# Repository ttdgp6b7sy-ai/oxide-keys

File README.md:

# Oxide Keys

A mini game console with 8 keys and a display, which has the ability to play very simple games to kill time and also a fun way to integrate Rust (the language I am learning).

The hardware is mainly composed of an 8-key mini game player with rotary encoder, LCD display that folds on a hinge, and RGB underglow on the Raspberry Pi Pico W, where I aim to include as much Rust as I can in this project.

## CAD views

[Assembly STEP](cad/OxideKeys-review-assembly-detailed.step) · [Enclosure SVG](cad/Oxidekeysenclosure.svg)

## Demo
No physical build yet but the image above shows the PCB board to be made.

## Location of stuff
- `firmware/` Rust code for the Pico W
- `pcb/` KiCad project and gerbers
- `cad/` 3D model and layout for enclosure
- `BOM.csv` parts list

## Quickstart

**Get the files**
Clone the repo or download extract zip from github repo.
`git clone https://github.com/ttdgp6b7sy-ai/oxide-keys.git`
`cd oxide-keys`

**Flash the firmware**
1. Hold the bootsel button on the pico W while plugging it into USB, it will appear as a drive.
2. Drag `firmware/oxide-keys.uf2` onto that drive and then it reboots on its own.

**Build the firmware yourself**
1. install rust from https://rustup.rs if you haven't already
2. `rustup target add thumbv6m-none-eabi`
3. `cargo install flip-link elf2uf2-rs --locked`
4. `cd firmware`, then `cargo build --release`
5.  convert to UF2: `elf2uf2-rs target/thumbv6m-none-eabi/release/oxide-keys oxide-keys.uf2`, then drag it onto the pico as above

**3d model**
The full assembly is `cad/OxideKeys-review-assembly-detailed.step`

## Features that I will implement
- The switches are designed so that each key is important in navigating the screen where I want to create a launcher which you can scroll through a section of simple games similar to pong and space invader that I create. These keys will be assigned certain roles in the future such as selecting, navigation (mimicking the hjkl keys etc), and the amount of keys allows a wide use-case in games that I will develop specifically for this device.
- The lights underneath the keys will be an amber glow until pressed in which they will react in a white colour once pressed.
- Want the encoder knob to be used to scroll on the idle screen/Launcher.

## Design
- Uses a pico W as the controller.
- firmware stack includes embedded hal, probers and rp2040 hal. It lives in firmware/ and builds with cargo build
- display sits on a hinge now
- fullparts list is in [BOM.csv](BOM.csv).
- the cad enclosure that I am incorporating uses a 2d laser cut acrylic with mounted standoffs in between. Meaning that I can still incorporate cool aesthetics with the layer being transparent on purpose.

## Todo
The potential of the encoder knob in some games is something I want to explore.

## Credits
credits to stardance for inspo + help.

## Bill of materials

The source BOM with supplier links is in [BOM.csv](BOM.csv).

| Part | Quantity | Price AUD | Supplier | Link |
| --- | ---: | ---: | --- | --- |
| Raspberry Pi Pico W | 1 | 9.90 | Core Electronics | [link](https://core-electronics.com.au/raspberry-pi-pico-w-wireless-wifi.html) |
| Piezo Buzzer | 1 | 0.34 | Core Electronics | [link](https://core-electronics.com.au/piezo-buzzer.html) |
| LiPo Battery 3.7V 1100mAh | 1 | 10.15 | Tempero Systems | [link](https://temperosystems.com.au/products/603450-lithium-ion-polymer-battery-lipo-3-7v-1100mah/) |
| Core Electronics Shipping | 1 | 7.00 | Core Electronics | [link](https://core-electronics.com.au/policies-faq) |
| Cherry MX2A Orange Switch pack (10x) | 1 | 6.50 | Mechstock | [link](https://www.mechstock.com.au/products/cherry-mx2a-orange) |
| Mechstock Shipping | 1 | 7.50 | Mechstock | [link](https://www.mechstock.com.au/pages/shipping-policy-2025) |
| Rotary Encoder Switch (SR1230) | 1 | 10.25 | Jaycar | [link](https://www.jaycar.com.au/rotary-encoder-switch-with-pushbutton/p/SR1230) |
| Silicone Wire 2m (28AWG Red + Black) | 1 | 4.95 | Amazon AU | [link](https://www.amazon.com.au/Ozchillon-28AWG-Flexible-Silicone-Black/dp/B0FTVY5H6M) |
| Pin Header Strip 40-way (M+F) | 1 | 2.95 | Jaycar | [link](https://www.jaycar.com.au/pcb-pins-and-headers/c/1HJ) |
| 1N4148 Diode Pack (5x) | 1 | 0.95 | Jaycar | [link](https://www.jaycar.com.au/1n4148-1n914-signal-diode-pack-of-5/p/ZR1100) |
| 2.4" TFT LCD Touch Display (ILI9341) | 1 | 10.00 | Createunsw | [link](https://store.createunsw.com.au/2-4-arduino-touchscreen-module) |
| M2 Nylon Standoff Kit (180pc) | 1 | 15.00 | Amazon AU | [link](https://www.amazon.com.au/Aolidsive-Standoff-Assortment-Motherboard-Projects/dp/B0GYBV21GF) |
| Clear Acrylic Sheet A5 3mm | 2 | 8.96 | Amazon AU | [link](https://www.amazon.com.au/Clear-Acrylic-Sheet-3mm-Thickness/dp/B0F4PN42ZM) |
| Knurled Encoder Knob (2pc) | 1 | 7.34 | Core-electronics | [link](https://core-electronics.com.au/slim-rubber-rotary-encoder-knob-11-5mm-x-14-5mm-d-shaft.html) |
| N3UD PBT Blank Keycaps 1U XDA Profile (20pc) | 1 | 7.00 | AliExpress | [link](https://www.aliexpress.com/w/wholesale-n3ud-20pcs-pbt-blank-keycap-xda.html) |
| Amazon AU Shipping (order remaining Amazon items together) | 1 | 0.00 | Amazon AU | [link](https://www.amazon.com.au/) |
| SK6812MINI RGB LED pack (x20) | 2 | 3.00 | KEEBD | [link](https://keebd.com/products/sk6812mini-rgb-led) |
| KEEBD Shipping | 1 | 9.59 | KEEBD | [link](https://keebd.com/) |
| TP4056 Li-ion Charger IC (harvest from domestic TP4056 module) | 1 | 3.99 | Tempero Systems | [link](https://temperosystems.com.au/products/tp4056-mini-usb-1a-5v-lithium-battery-charger-copy/) |
| AP2112K-3.3 LDO Regulator | 1 | 5.23 | Amazon AU | [link](https://www.amazon.com.au/) |
| 330 Ohm 0805 Resistor pack (10x) | 1 | 1.40 | Altronics | [link](https://www.altronics.com.au/electronic-components/carbon-film-resistors/?prdv=330R) |
| 1uF 0805 Capacitor pack (50x) | 1 | 13.95 | Phipps Electronics | [link](https://www.phippselectronics.com/product/16v-1uf-0805-ceramic-smd-capacitor-pack-of-50/) |
| Brass Hinges (2-pack) | 1 | 7.94 | Bunnings | [link](https://www.bunnings.com.au/prestige-15-x-25-x-0-5mm-decorative-brass-hinges_p3968293) |
| Bunnings Shipping | 1 | 0.00 | Bunnings | [link](https://www.bunnings.com.au/) |
| TOTAL (including PCB fabrication) |  | 161.79 |  |  |
| JLCPCB 4-Layer PCB Fab | 1 | 13.00 | JLCPCB | [link](https://jlcpcb.com/) |
| --- Optional, not counted above --- |  |  |  |  |
| Desertcart M2 Mounting Screw Kit (60pc) | 1 | 10.00 | Desertcart Australia | [link](https://www.desertcart.com.au/products/600128736-m2-ssd-screws-kit-pcie-nvme-m-2-ssd-mounting) |
| Soldering Iron Kit (optional) | 1 | 25.00 | Amazon AU | [link](https://www.amazon.com.au/Soldering-Iron-Kit-Rechargeable-Temperature/dp/B0DYH7QMYK) |

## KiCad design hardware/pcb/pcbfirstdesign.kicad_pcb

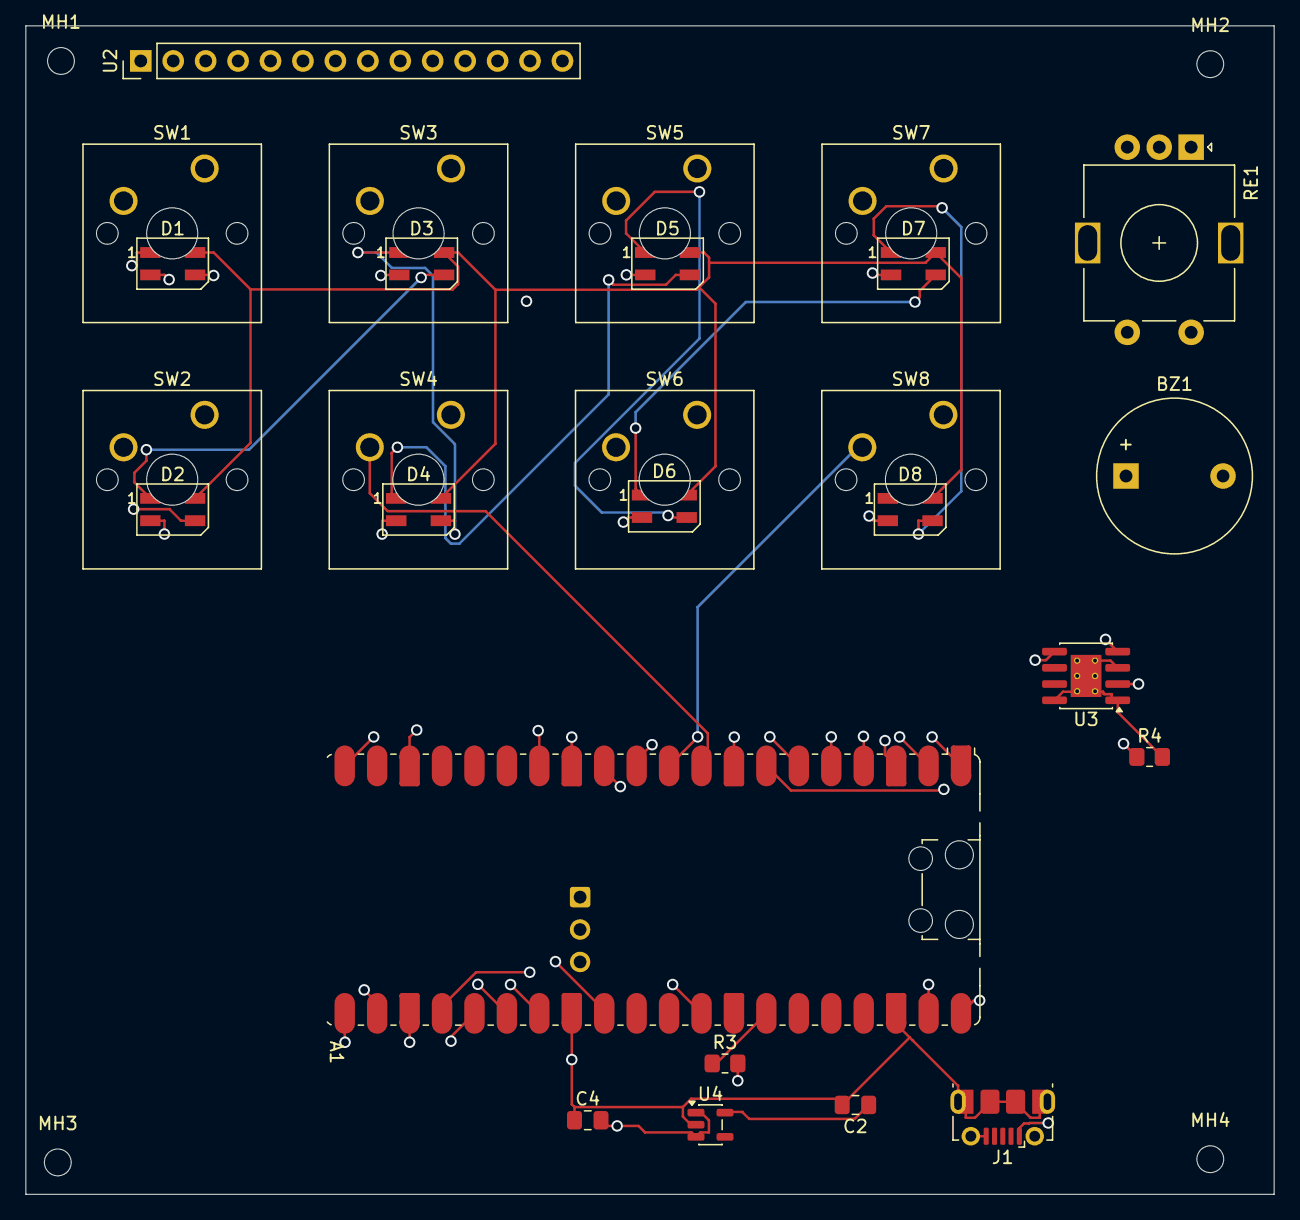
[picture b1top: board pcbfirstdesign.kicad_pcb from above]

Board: 4 copper layers, 97.8 x 91.5 mm, 31 parts (0 on the bottom side), 34 nets.

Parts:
A1: RaspberryPi_Pico_W; RaspberryPi_Pico_W_SMD_HandSolder
BZ1: Buzzer; Buzzer_12x9.5RM7.6
C2, C4: C; C_0805_2012Metric_Pad1.18x1.45mm_HandSolder
D1, D2, D3, D4, D5, D6, D7, D8: SK6812MINI; LED_SK6812MINI_PLCC4_3.5x3.5mm_P1.75mm
J1: USB_B_Micro; USB_Micro-B_Molex-105017-0001
MH1, MH2, MH3, MH4: MountingHole_2.1mm
R3, R4: R; R_0805_2012Metric_Pad1.20x1.40mm_HandSolder
RE1: RotaryEncoder; RotaryEncoder_Alps_EC11E-Switch_Vertical_H20mm
SW1, SW2, SW3, SW4, SW5, SW6, SW7, SW8: SW_Push; SW_Cherry_MX_1.00u_PCB
U2: CR2013-MI2120; PinHeader_1x14_P2.54mm_Vertical
U3: TP4056-42-ESOP8; SOIC-8-1EP_3.9x4.9mm_P1.27mm_EP2.41x3.3mm_ThermalVias
U4: AP2112K-3.3; SOT-23-5

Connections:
+3.3V_LED: D1.4 (VDD), D2.4 (VDD), D3.4 (VDD), D4.4 (VDD), D5.4 (VDD), D6.4 (VDD), D7.4 (VDD), D8.4 (VDD)
+BATT: A1.39 (VSYS), C4.2, U3.5 (BAT), U4.1 (VIN), U4.3 (EN)
/SPI_SCK: A1.24 (GPIO18), U2.7 (SCK), U2.13 (SD_SCK)
GND: A1.3 (GND), A1.8 (GND), A1.13 (GND), A1.18 (GND), A1.23 (GND), A1.28 (GND), A1.38 (GND), BZ1.2 (-), C2.2, C4.1, D1.2 (VSS), D2.2 (VSS), D3.2 (VSS), D4.2 (VSS), D5.2 (VSS), D6.2 (VSS), D7.2 (VSS), D8.2 (VSS), J1.5 (GND), J1.SH (Shield), R4.2, SW1.1, SW2.1, SW3.1, SW4.1, SW6.1, SW7.1, SW8.1, U2.2 (GND), U3.1 (TEMP), U3.3 (GND), U3.8 (CE), U3.9 (EPAD), U4.2 (GND)
unnamed: A1.1 (GPIO0), SW1.2, SW5.1
unnamed: A1.2 (GPIO1), SW5.2
unnamed: A1.4 (GPIO2), SW2.2
unnamed: A1.5 (GPIO3), SW6.2
unnamed: A1.6 (GPIO4), SW3.2
unnamed: A1.7 (GPIO5), SW7.2
unnamed: A1.9 (GPIO6), SW4.2
unnamed: A1.10 (GPIO7), SW8.2
unnamed: A1.11 (GPIO8), RE1.B
unnamed: A1.12 (GPIO9), RE1.C
unnamed: A1.14 (GPIO10), RE1.A
unnamed: A1.20 (GPIO15), BZ1.1 (+)
unnamed: A1.21 (GPIO16), A1.25 (GPIO19), U2.6 (MOSI), U2.9 (MISO), U2.11 (SD_MOSI), U2.12 (SD_MISO)
unnamed: A1.22 (GPIO17), U2.4 (RESET)
unnamed: A1.26 (GPIO20), U2.8 (LED)
unnamed: A1.27 (GPIO21), U2.3 (~CS), U2.10 (SD_CS)
unnamed: A1.29 (GPIO22), U2.5 (D/~C)
unnamed: A1.32 (GPIO27_ADC1), U2.14 (FLASH_CD)
unnamed: A1.34 (GPIO28_ADC2), R3.1
unnamed: A1.40 (VBUS), J1.1 (VBUS), U3.4 (V_{CC})
unnamed: D1.3 (DIN), R3.2
unnamed: D1.1 (DOUT), D2.3 (DIN)
unnamed: D2.1 (DOUT), D3.3 (DIN)
unnamed: D3.1 (DOUT), D4.3 (DIN)
unnamed: D4.1 (DOUT), D5.3 (DIN)
unnamed: D5.1 (DOUT), D6.3 (DIN)
unnamed: D6.1 (DOUT), D7.3 (DIN)
unnamed: D7.1 (DOUT), D8.3 (DIN)
unnamed: R4.1, U3.2 (PROG)
unnamed: C2.1, U4.5 (VOUT)

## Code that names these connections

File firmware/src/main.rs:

#![no_std]
#![no_main]

use embedded_graphics::pixelcolor::Rgb565;
use embedded_graphics::prelude::RgbColor;
use embedded_hal::delay::DelayNs;
use embedded_hal::digital::OutputPin;
use panic_halt as _;
use rp2040_hal as hal;
use hal::clocks::Clock;
use hal::pac;

mod buzzer;
mod display;
mod encoder;
mod leds;
mod switches;

use switches::SwitchId;

#[link_section = ".boot2"]
#[used]
pub static BOOT2: [u8; 256] = rp2040_boot2::BOOT_LOADER_GENERIC_03H;

const XTAL_FREQ_HZ: u32 = 12_000_000;

#[rp2040_hal::entry]
fn main() -> ! {
    let mut peripherals = pac::Peripherals::take().unwrap();

    let mut watchdog = hal::Watchdog::new(peripherals.WATCHDOG);

    // set up the clocks, this depends on the crystal on the board
    let clocks = hal::clocks::init_clocks_and_plls(
        XTAL_FREQ_HZ,
        peripherals.XOSC,
        peripherals.CLOCKS,
        peripherals.PLL_SYS,
        peripherals.PLL_USB,
        &mut peripherals.RESETS,
        &mut watchdog,
    )
    .expect("clock init failed");

    let mut timer = rp2040_hal::Timer::new(peripherals.TIMER, &mut peripherals.RESETS, &clocks);

    let sio = hal::Sio::new(peripherals.SIO);
    let pins = hal::gpio::Pins::new(
        peripherals.IO_BANK0,
        peripherals.PADS_BANK0,
        sio.gpio_bank0,
        &mut peripherals.RESETS,
    );

    let mut led = pins.gpio25.into_push_pull_output();

    // the 8 switches on the panel, see switches.rs for which pin is which
    let mut switches = switches::Switches::new(
        pins.gpio0.into_pull_up_input(),
        pins.gpio1.into_pull_up_input(),
        pins.gpio2.into_pull_up_input(),
        pins.gpio4.into_pull_up_input(),
        pins.gpio6.into_pull_up_input(),
        pins.gpio3.into_pull_up_input(),
        pins.gpio5.into_pull_up_input(),
        pins.gpio7.into_pull_up_input(),
    );

    let mut encoder = encoder::Encoder::new(
        pins.gpio10.into_pull_up_input(),
        pins.gpio8.into_pull_up_input(),
        pins.gpio9.into_push_pull_output(),
    );

    let mut buzzer = buzzer::Buzzer::new(peripherals.PWM, &mut peripherals.RESETS, pins.gpio15);
    buzzer.stop(); // don't want it making noise on startup

    // 2.4" ili9341 screen on spi0, miso is wired up but don't use it
    let mut display = display::build(
        peripherals.SPI0,
        &mut peripherals.RESETS,
        clocks.peripheral_clock.freq(),
        pins.gpio18, // sck
        pins.gpio19, // mosi
        pins.gpio16, // miso
        pins.gpio17, // cs
        pins.gpio20, // dc
        pins.gpio21, // reset
        pins.gpio22, // backlight
        &mut timer,
    );

    let mut encoder_count = 0;
    let mut displayed_count = i32::MIN;
    let mut displayed_any_pressed = false;
    let mut number_buffer = [0u8; 8];

    loop {
        let now_ms = timer.get_counter().ticks() / 1000;
        switches.upd(now_ms);

        match encoder.upd() {
            encoder::Rot::Cw => encoder_count += 1,
            encoder::Rot::Ccw => encoder_count -= 1,
            encoder::Rot::None => {}
        }

        let mut any_pressed = false;
        for switch_id in SwitchId::ALL {
            if switches.pressed(switch_id) {
                any_pressed = true;
            }
        }

        // turn the status led on while any switch is held down
        if any_pressed {
            led.set_high().unwrap();
        } else {
            led.set_low().unwrap();
        }

        let display_changed =
            encoder_count != displayed_count || any_pressed != displayed_any_pressed;

        // only redraw about 5 times a second, and only if something changed
        if display_changed && now_ms % 200 < 20 {
            displayed_count = encoder_count;
            displayed_any_pressed = any_pressed;

            display.clear(Rgb565::BLACK);
            display.text("RP2040 PANEL", 10, 10, Rgb565::GREEN);

            let mut dot_x: i32 = 20;
            for switch_id in SwitchId::ALL {
                let color = if switches.pressed(switch_id) {
                    Rgb565::GREEN
                } else {
                    Rgb565::new(15, 30, 15) // dim gray, there's no gray constant
                };

                display.dot(dot_x, 35, color);
                dot_x += 26;
            }

            display.text("ENC:", 10, 65, Rgb565::WHITE);
            display.text(
                format_number(encoder_count, &mut number_buffer),
                55,
                65,
                Rgb565::WHITE,
            );
        }

        timer.delay_ms(10);
    }
}

// turns a number into text by hand since no_std and have no heap
fn format_number(number: i32, buffer: &mut [u8; 8]) -> &str {
    let is_negative = number < 0;
    let mut value = number.unsigned_abs();
    let mut index = buffer.len();

    if value == 0 {
        index -= 1;
        buffer[index] = b'0';
    }

    while value > 0 {
        index -= 1;
        buffer[index] = b'0' + (value % 10) as u8;
        value /= 10;
    }

    if is_negative {
        index -= 1;
        buffer[index] = b'-';
    }

    core::str::from_utf8(&buffer[index..]).unwrap()
}
